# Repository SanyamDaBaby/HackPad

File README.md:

# Orpheuspad

# BOM:
- 5x Cherry MX switches
- 1x EC11 Encoder
- 1x PCB
- 1x WS2812B LEDs
- 4x M3 12mm Bolts

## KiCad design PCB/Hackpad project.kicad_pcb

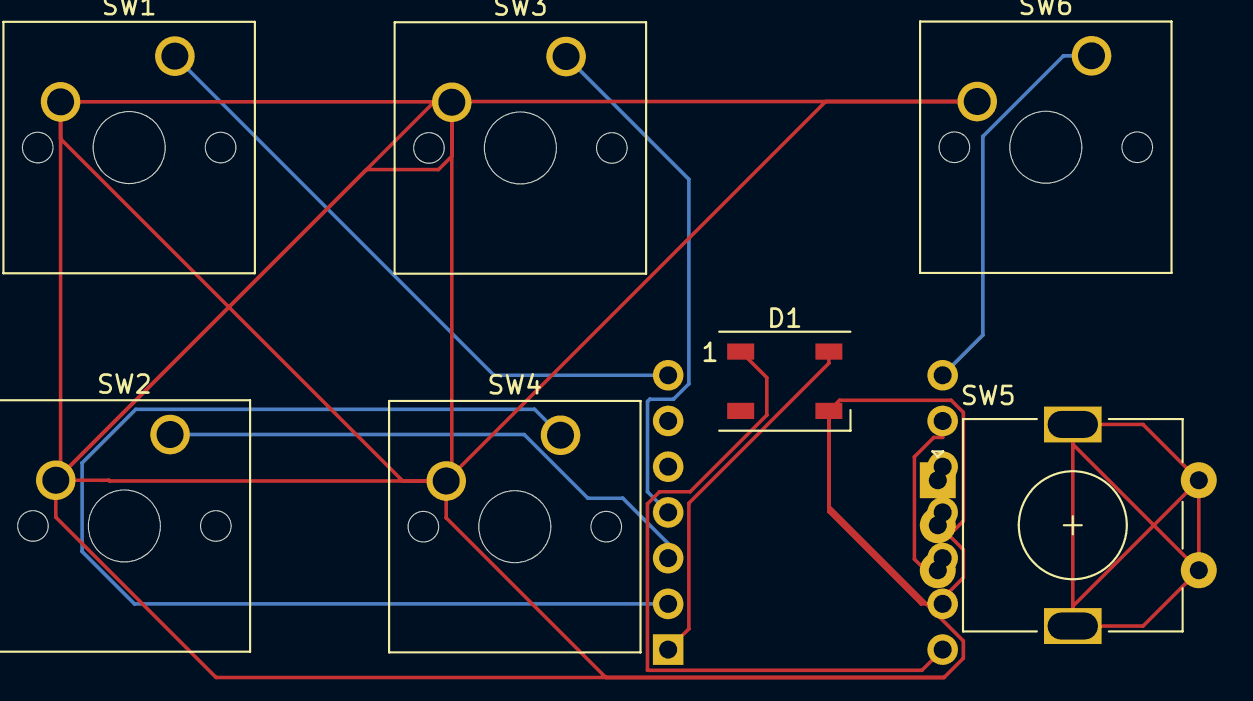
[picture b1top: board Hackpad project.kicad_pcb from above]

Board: 2 copper layers, 8 parts (1 on the bottom side), 10 nets.

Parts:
D1: WS2812B; LED_WS2812B_PLCC4_5.0x5.0mm_P3.2mm
SW1, SW2, SW3, SW4, SW6: SW_Push; SW_Cherry_MX_1.00u_PCB
SW5: RotaryEncoder; RotaryEncoder_Alps_EC11E-Switch_Vertical_H20mm
U1: Seeed Studio XIAO SAMD21; XIAO-Generic-Thruhole-14P-2.54-21X17.8MM

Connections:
GND: D1.3 (VSS), SW1.2, SW2.2, SW3.2, SW4.2, SW5.C, SW6.2, U1.13 (GND)
unnamed: D1.4 (DIN), U1.1 (PA02_A0_D0)
unnamed: D1.1 (VDD), U1.14 (5V)
unnamed: SW4.1, U1.2 (PA4_A1_D1)
unnamed: SW5.A, U1.10 (PA5_A9_D9_MISO)
unnamed: SW5.B, U1.9 (PA7_A8_D8_SCK)
unnamed: SW2.1, U1.3 (PA10_A2_D2)
unnamed: SW3.1, U1.4 (PA11_A3_D3)
unnamed: SW1.1, U1.7 (PB08_A6_D6_TX)
unnamed: SW6.1, U1.8 (PB09_A7_D7_RX)

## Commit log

2024-10-06 MCU set up
2024-10-14 CAD + PCB
